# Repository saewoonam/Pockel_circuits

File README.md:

# Kicad projects for making the pockel cell controller
## List of parts
* circuit board -> DAC and digital IO:  DAC_pockel
* make front and back panel for the enclosure out of printed circuit board -> Front panel with DB9 connector: Pockel_front
* Enclosure from thorlabs: EED3011,  [link](https://www.thorlabs.com/newgrouppage9.cfm?objectgroup_ID=8681)

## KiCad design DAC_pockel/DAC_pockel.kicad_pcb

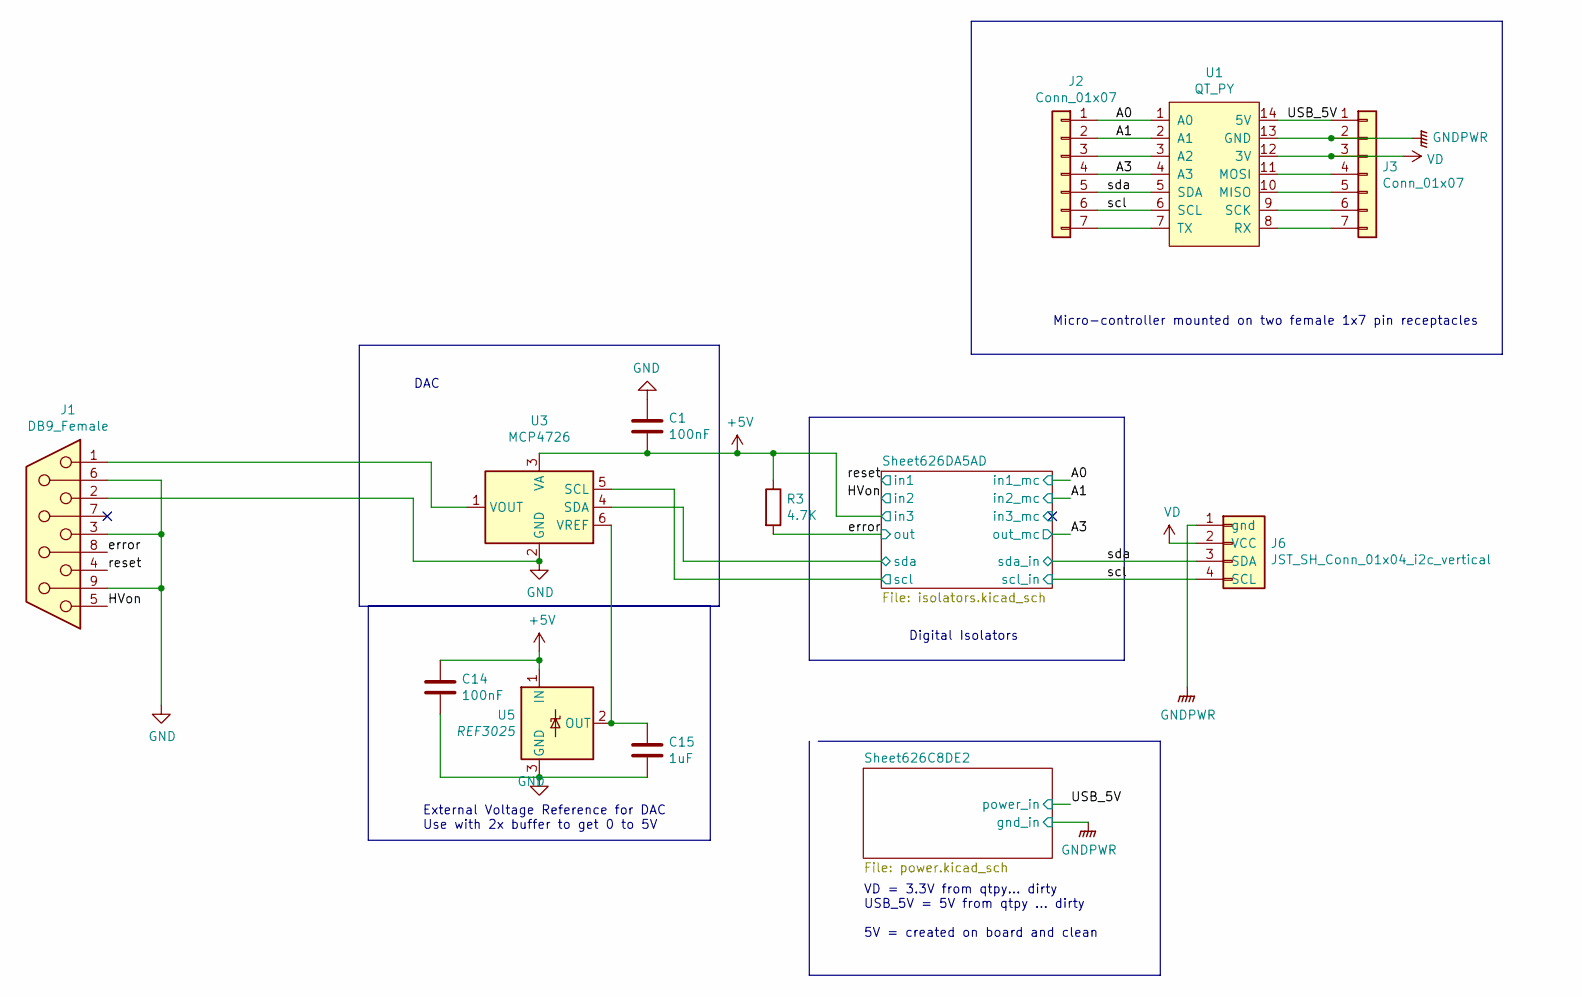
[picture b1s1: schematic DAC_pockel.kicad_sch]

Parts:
C1, C14: 100nF; C_0603_1608Metric_Pad1.05x0.95mm_HandSolder; MPN CC0603KRX7R9BB104; LCSC C14663
C15: 1uF; C_0603_1608Metric_Pad1.05x0.95mm_HandSolder; MPN CL10A105KB8NNNC; LCSC C15849
J1: DB9_Female; DSUB-TH_DS1037-09FNAKT74-0CC; MPN DS1037-09FNAKT74-0CC; LCSC C75749
J2, J3: Conn_01x07; PinSocket_1x07_P2.54mm_Vertical; LCSC C358721
J6: JST_SH_Conn_01x04_i2c_vertical; JST_SH_BM04B-SRSS-TB_1x04-1MP_P1.00mm_Vertical; MPN A1001WV-S-04PD01; LCSC C371602
R3: 4.7K; R_0603_1608Metric_Pad1.05x0.95mm_HandSolder; MPN 0603WAF4701T5E; LCSC C23162
U1: QT_PY
U3: MCP4726; SOT-23-6; MPN MCP4726A0T-E/CH; LCSC C191581
U5: REF3025; SOT-23

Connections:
+5V: C1.2, C14.1, R3.1, U3.3 (VA), U5.1 (IN); also elsewhere on the board
/A0: J2.1, U1.1 (A0); also elsewhere on the board
/A1: J2.2, U1.2 (A1); also elsewhere on the board
/A3: J2.4, U1.4 (A3); also elsewhere on the board
/HVon: J1.5; also elsewhere on the board
/Sheet626DA5AD/scl: U3.5 (SCL); also elsewhere on the board
/Sheet626DA5AD/sda: U3.4 (SDA); also elsewhere on the board
/USB_5V: J3.1, U1.14 (5V); also elsewhere on the board
/error: J1.8, R3.2; also elsewhere on the board
/reset: J1.4; also elsewhere on the board
/scl: J2.6, J6.4 (SCL), U1.6 (SCL); also elsewhere on the board
/sda: J2.5, J6.3 (SDA), U1.5 (SDA); also elsewhere on the board
GND: C1.1, C14.2, C15.2, J1.2, J1.3, J1.6, J1.9, U3.2 (GND), U5.3 (GND); also elsewhere on the board
GNDPWR: J3.2, J6.1 (gnd), U1.13 (GND); also elsewhere on the board
unnamed: C15.1, U3.6 (VREF), U5.2 (OUT)
unnamed: J1.1, U3.1 (VOUT)
unnamed: J2.3, U1.3 (A2)
unnamed: J2.7, U1.7 (TX)
unnamed: J3.4, U1.11 (MOSI)
unnamed: J3.5, U1.10 (MISO)
unnamed: J3.6, U1.9 (SCK)
unnamed: J3.7, U1.8 (RX)
VD: J3.3, J6.2 (VCC), U1.12 (3V); also elsewhere on the board

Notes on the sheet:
VD = 3.3V from qtpy… dirty USB_5V = 5V from qtpy … dirty 5V = created on board and clean
DAC
Digital Isolators
Micro-controller mounted on two female 1x7 pin receptacles
External Voltage Reference for DAC Use with 2x buffer to get 0 to 5V

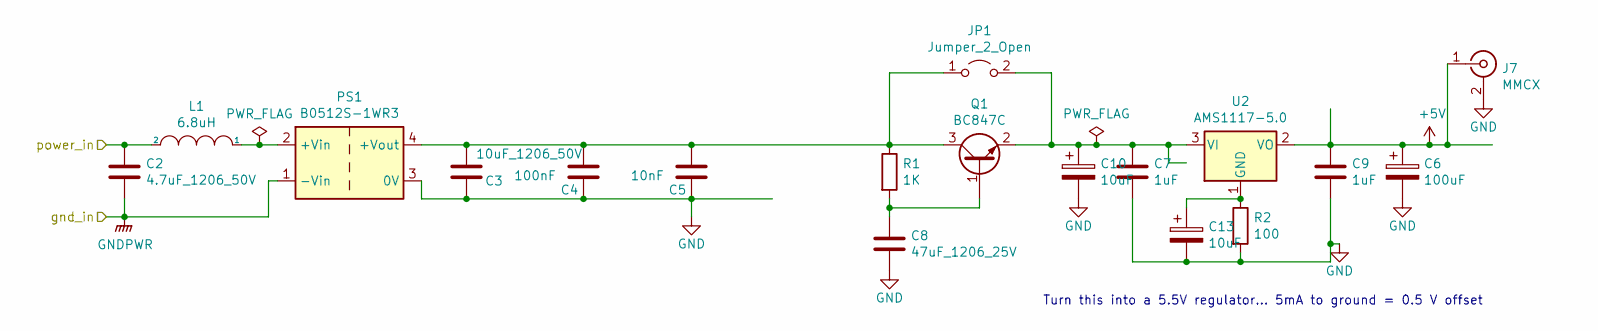
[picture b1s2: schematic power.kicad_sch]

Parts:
C2: 4.7uF_1206_50V; C_1206_3216Metric_Pad1.42x1.75mm_HandSolder; MPN 1206B475K500NT; LCSC C29823
C3: 10uF_1206_50V; C_1206_3216Metric_Pad1.42x1.75mm_HandSolder; MPN CL31A106KBHNNNE; LCSC C13585
C4: 100nF; C_0603_1608Metric_Pad1.05x0.95mm_HandSolder; MPN CC0603KRX7R9BB104; LCSC C14663
C5: 10nF; C_0603_1608Metric_Pad1.05x0.95mm_HandSolder; MPN 0603B103K500NT; LCSC C57112
C6: 100uF; CP_EIA-3528-12_Kemet-T; MPN GRM32ER61A107ME20L; LCSC C84455
C7, C9: 1uF; C_0603_1608Metric_Pad1.05x0.95mm_HandSolder; MPN CL10A105KB8NNNC; LCSC C15849
C8: 47uF_1206_25V; C_1206_3216Metric_Pad1.42x1.75mm_HandSolder; MPN GRM31CR61E476ME44L; LCSC C403725
C10, C13: 10uF; CP_EIA-3216-18_Kemet-A; MPN TAJA106K016RNJ; LCSC C7171
J7: MMCX; MMCX_JLC; MPN KH-MMCX-Z; LCSC C530664
JP1: Jumper_2_Open; SolderJumper-2_P1.3mm_Open_RoundedPad1.0x1.5mm
L1: 6.8uH; L_1210_3225Metric_Pad1.42x2.65mm_HandSolder; MPN NLCV32T-6R8M-PFR; LCSC C87559
PS1: B0512S-1WR3; Converter_DCDC_muRata_CRE1xxxxxx3C_THT; MPN B0512S-1WR3; LCSC C133158
Q1: BC847C; SOT-23; MPN BC847C,215; LCSC C8664
R1: 1K; R_0603_1608Metric_Pad1.05x0.95mm_HandSolder; MPN 0603WAF1001T5E; LCSC C21190
R2: 100; R_0603_1608Metric_Pad1.05x0.95mm_HandSolder; MPN 0603WAF1000T5E; LCSC C22775
U2: AMS1117-5.0; SOT-223-3_TabPin2

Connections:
+5V: C6.1, C9.1, J7.1 (In), U2.2 (VO); also elsewhere on the board
/USB_5V: C2.1, L1.2; also elsewhere on the board
GND: C3.2, C4.1, C5.1, C6.2, C7.2, C8.2, C9.2, C10.2, C13.2, J7.2 (Ext), PS1.3 (0V), R2.2; also elsewhere on the board
GNDPWR: C2.2, PS1.1 (-Vin); also elsewhere on the board
unnamed: C3.1, C4.2, C5.2, JP1.1 (A), PS1.4 (+Vout), Q1.3 (C), R1.1
unnamed: C8.1, Q1.1 (B), R1.2
unnamed: C7.1, C10.1, JP1.2 (B), Q1.2 (E), U2.3 (VI)
unnamed: C13.1, R2.1, U2.1 (GND)
unnamed: L1.1, PS1.2 (+Vin)

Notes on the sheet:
Turn this into a 5.5V regulator… 5mA to ground = 0.5 V offset

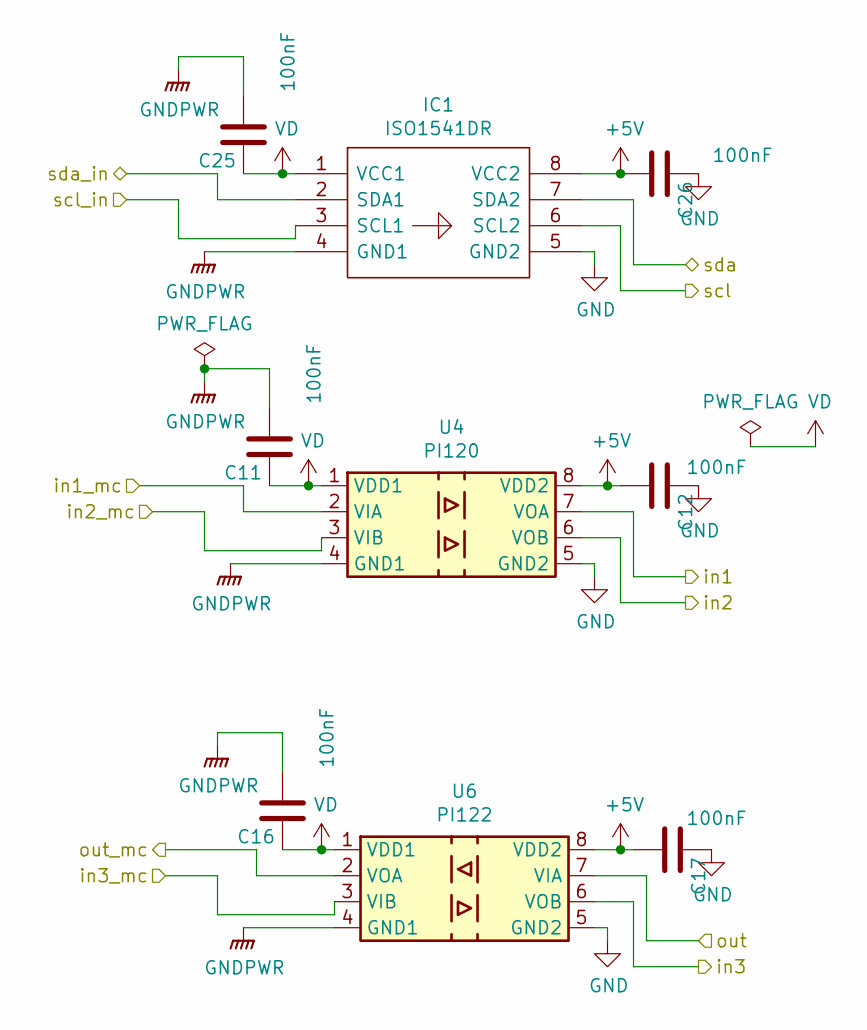
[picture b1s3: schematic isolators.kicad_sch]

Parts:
C11, C12, C16, C17, C25, C26: 100nF; C_0603_1608Metric_Pad1.05x0.95mm_HandSolder; MPN CC0603KRX7R9BB104; LCSC C14663
IC1: ISO1541DR; SOIC-8_3.9x4.9mm_P1.27mm; MPN ISO1541DR; LCSC C143028
U4: PI120; SOIC-8_3.9x4.9mm_P1.27mm; MPN π120U30; LCSC C471591
U6: PI122; SOIC-8_3.9x4.9mm_P1.27mm; MPN π122U31; LCSC C471590

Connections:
+5V: C12.2, C17.2, C26.2, IC1.8 (VCC2), U4.8 (VDD2), U6.6 (VOB), U6.8 (VDD2); also elsewhere on the board
/A0: U4.2 (VIA); also elsewhere on the board
/A1: U4.3 (VIB); also elsewhere on the board
/A3: U6.2 (VOA); also elsewhere on the board
/HVon: U4.6 (VOB); also elsewhere on the board
/Sheet626DA5AD/in3_mc: U6.3 (VIB)
/Sheet626DA5AD/scl: IC1.6 (SCL2); also elsewhere on the board
/Sheet626DA5AD/sda: IC1.7 (SDA2); also elsewhere on the board
/error: U6.7 (VIA); also elsewhere on the board
/reset: U4.7 (VOA); also elsewhere on the board
/scl: IC1.3 (SCL1); also elsewhere on the board
/sda: IC1.2 (SDA1); also elsewhere on the board
GND: C12.1, C17.1, C26.1, IC1.5 (GND2), U4.5 (GND2), U6.5 (GND2); also elsewhere on the board
GNDPWR: C11.2, C16.2, C25.2, IC1.4 (GND1), U4.4 (GND1), U6.4 (GND1); also elsewhere on the board
VD: C11.1, C16.1, C25.1, IC1.1 (VCC1), U4.1 (VDD1), U6.1 (VDD1); also elsewhere on the board

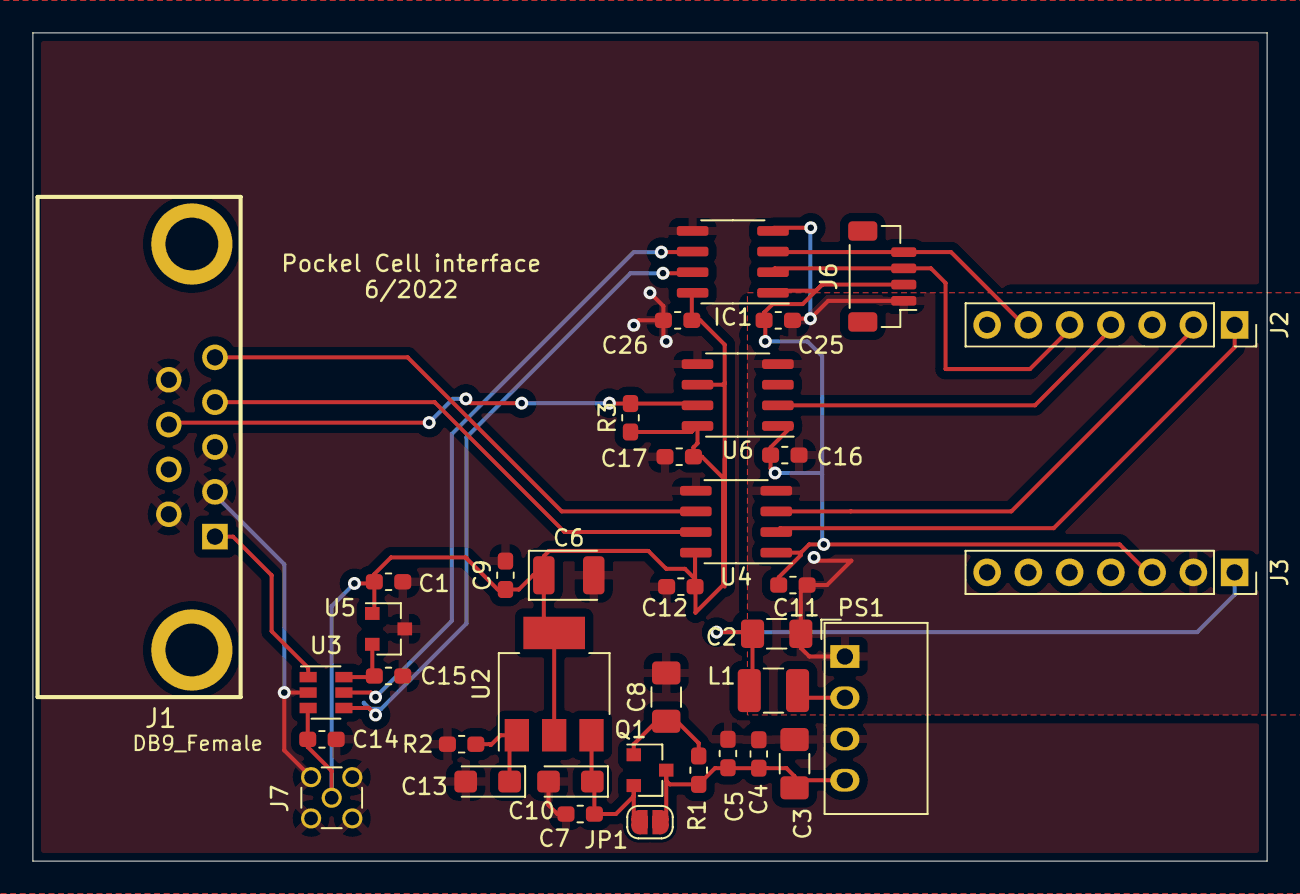
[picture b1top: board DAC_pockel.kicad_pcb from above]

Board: 2 copper layers, 76.0 x 51.0 mm, 37 parts (0 on the bottom side), 22 nets.

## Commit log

2022-06-29 Added Pockel_back panel
    Added Pockel_back panel with cutout for micro-USB
